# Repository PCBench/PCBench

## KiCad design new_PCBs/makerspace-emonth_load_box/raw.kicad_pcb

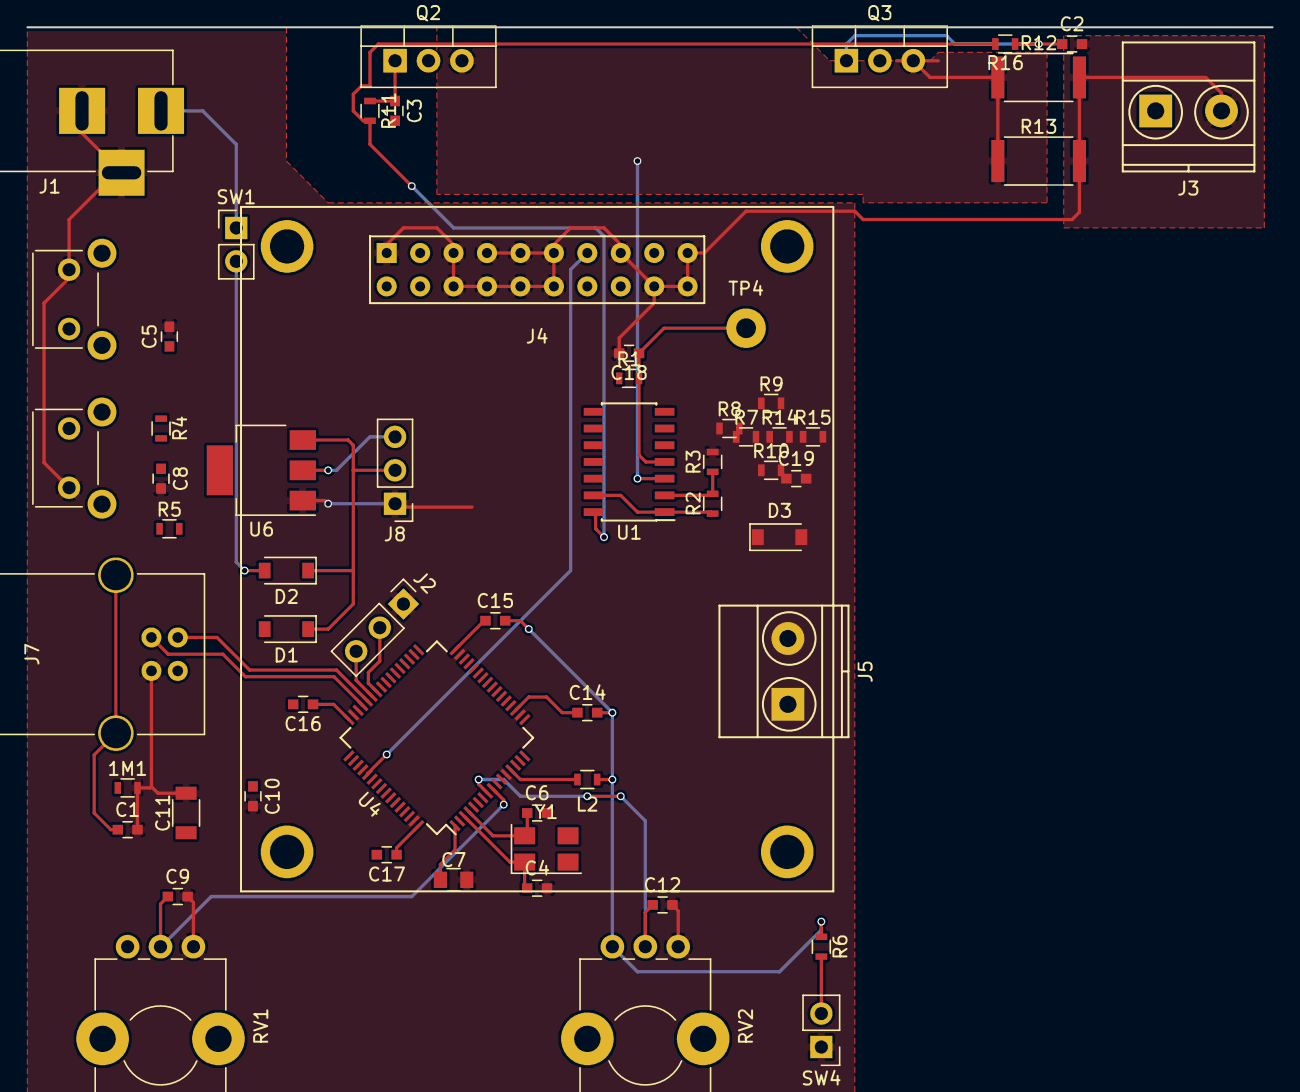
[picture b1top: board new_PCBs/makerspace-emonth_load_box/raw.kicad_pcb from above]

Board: 2 copper layers, 59 parts (0 on the bottom side), 41 nets.

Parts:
1M1: R; R_0603
C1: 4n7; C_0603
C2, C3, C5, C8, C9, C12, C18: 0.1; C_0603
C4, C6, C14, C15, C16, C17: C; C_0603
C7: 1.0; C_0805
C10: 0.1u; C_0603
C11: 10u; C_1206
C19: 4.7n; C_0603
D1, D2: D; D_SOD-123
D3: D_Schottky; D_SOD-123
J1: BARREL_JACK
J2, J8: CONN_01X03; Socket_Strip_Straight_1x03_Pitch2.54mm
J3, J5: Screw_Terminal_1x02; TerminalBlock_Pheonix_MKDS1.5-2pol
J4: CONN_02X10; NHD-1.69
J7: USB_B
L2: Ferrite_Bead; L_0603
Q2, Q3: FQP30N06L; TO-220_Vertical
R1, R4, R11, R16: 100R; R_0603
R2: 24K; R_0603
R3, R6, R9, R14: 10K; R_0603
R5, R10: 4.7K; R_0603
R7, R8, R15: 100K; R_0603
R12, R13: 0R1; R_2512
RV1, RV2: POT; Potentiometer_Alps_RK09K_Horizontal
SW1: SW_SPST; Socket_Strip_Straight_1x02_Pitch2.54mm
SW2, SW3: SW_Push; SW_Tactile_SKHH_Angled
SW4: SW_Push; Pin_Header_Straight_1x02_Pitch2.54mm
TP4: TEST; Measurement_Point_Round-TH_Big
U1: LM324; SOIC-14_3.9x8.7mm_Pitch1.27mm
U4: STM32L152RCTx; LQFP-64_10x10mm_Pitch0.5mm
U6: LD1117S33TR; SOT-223
Y1: Crystal_GND23; Crystal_SMD_5032-4pin_5.0x3.2mm

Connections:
+3V3: C11.1, C14.2, C15.2, C16.2, C17.2, D3.1, J4.2, J8.3, L2.1, R1.1, R5.1, R6.1, RV1.1, RV2.1, U6.2
+12V: D2.2, SW1.2
+BATT: C10.1, D1.1, D2.1, J8.2, U6.3
/load_box_display/MOSI: J4.13, U4.53
/load_box_interface/GO_BUTTON: R6.2, SW4.2
/load_box_interface/STATIC_VREF: C12.1, RV2.2, U4.8
/load_box_interface/STEP_VREF: C9.1, RV1.2, U4.9
/load_box_interface/USER_BUTTON: R4.1, R5.2, SW3.1, U4.2
/load_box_mcu/CHOSEN_VREF: U1.12, U4.40
/load_box_mcu/USB_DM: J7.2, U4.44
/load_box_mcu/USB_DP: J7.3, U4.45
/load_box_sink/REMOTE_SENSE_OUT: C19.1, D3.2, R15.2
GND: 1M1.2, C1.2, C2.2, C3.2, C4.2, C5.2, C6.2, C7.2, C8.2, C9.2, C10.2, C11.2, C12.2, C18.2, C19.2, J1.2, J1.3, J2.1, J3.2, J4.1, J4.5, J4.6, J4.7, J4.8, J4.9, J4.10, J4.11, J4.12, J4.15, J4.18, J4.19, J4.20, J7.4, J8.1, R3.2, R9.2, R10.1, R12.2, R13.2, RV1.3, RV2.3, SW2.1, SW3.2, SW4.1, U4.12, U4.18, U4.31, U4.47, U4.63, U6.1
NRST: C5.1, SW2.2, U4.7
unnamed: 1M1.1, C1.1, J7.5
unnamed: C2.1, Q3.1, R16.1
unnamed: C3.1, Q2.1, R11.1
unnamed: C4.1, U4.3, Y1.1
unnamed: C6.1, U4.4, Y1.4
unnamed: C7.1, U4.1
unnamed: C8.1, R4.2
unnamed: C14.1, U4.19
unnamed: C15.1, U4.32
unnamed: C16.1, U4.48
unnamed: C17.1, U4.64
unnamed: C18.1, R1.2, TP4.1, U1.4
unnamed: D1.2, J7.1
unnamed: J1.1, SW1.1
unnamed: J2.2, U4.42
unnamed: J2.3, U4.43
unnamed: J3.1, Q2.2, Q3.2
unnamed: J5.1, R7.2
unnamed: J5.2, R8.2
unnamed: L2.2, U4.13
unnamed: Q2.3, Q3.3, R12.1, R13.1, U1.3
unnamed: R2.1, U1.1, U1.13
unnamed: R2.2, R3.1, U1.2
unnamed: R7.1, R9.1, U1.10
unnamed: R8.1, R10.2, R14.1, U1.9
unnamed: R11.2, R16.2, U1.14
unnamed: R14.2, R15.1, U1.8

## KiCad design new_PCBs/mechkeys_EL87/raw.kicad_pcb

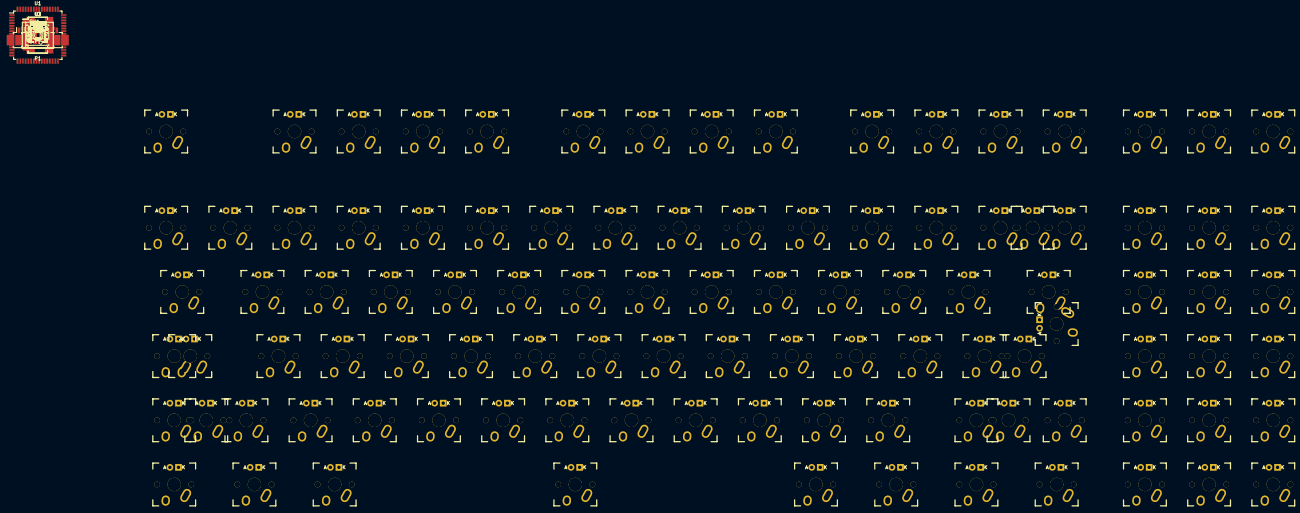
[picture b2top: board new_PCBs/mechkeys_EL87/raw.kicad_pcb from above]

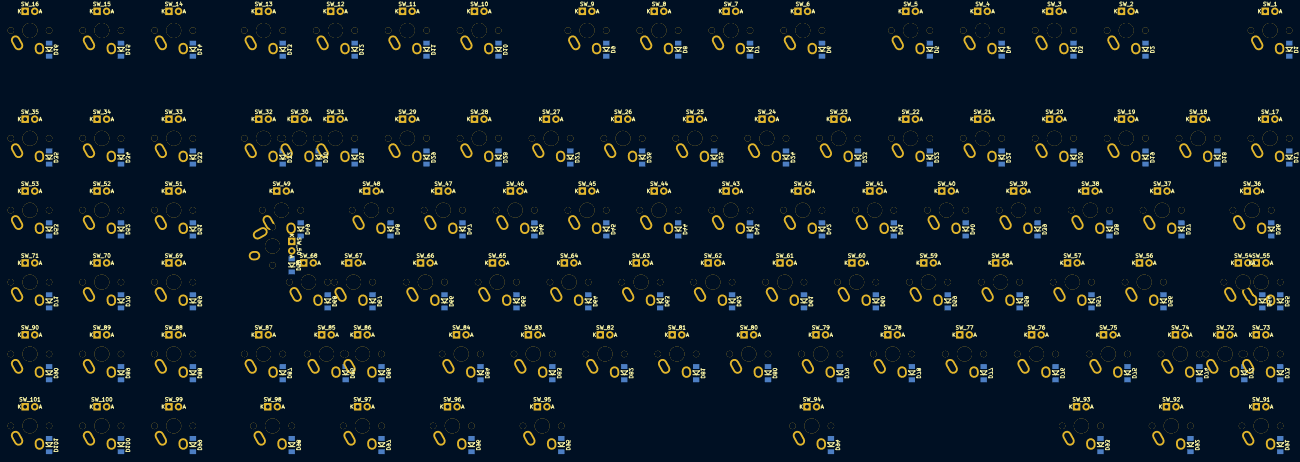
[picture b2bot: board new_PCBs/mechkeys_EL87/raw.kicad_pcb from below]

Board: 2 copper layers, 272 parts (101 on the bottom side), 189 nets, no tracks yet.

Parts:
C1, C2: 18pF; C_0805_HandSoldering
C3, C6, C7, C8, C9, C11, C12, C14, C15: 0.1µF; C_0805_HandSoldering
C4, C10, C13: 1µF; C_0805_HandSoldering
C5: 4.7µF; Tantalum_Case-S_EIA-3216-12_Reflow
D1, D2, D3, D4, D5, D6, D7, D8, D9, D10, D11, D12, D13, D14, D15, D16, D17, D18, D19, D20, D21, D22, D23, D24, D25, D26, D27, D28, D29, D30, D31, D32, D33, D34, D35, D36, D37, D38, D39, D40, D41, D42, D43, D44, D45, D46, D47, D48, D49, D50, D51, D52, D53, D54, D55, D56, D57, D58, D59, D60, D61, D62, D63, D64, D65, D66, D67, D68, D69, D70, D71, D72, D73, D74, D75, D76, D77, D78, D79, D80, D81, D82, D83, D84, D85, D86, D87, D88, D89, D90, D91, D92, D93, D94, D95, D96, D97, D98, D99, D100, D101: D; MiniMELF_Standard
F1: FP_Small; R_1206_HandSoldering
P1: USB_OTG; USB_Mini-B
P2: CONN_02X03; Molex_PicoBlade_53261-0671_06x1.25mm_Angled
P3: CONN_02X05; Molex_PicoBlade_53261-1071_10x1.25mm_Angled
P4: CONN_01X03; Molex_PicoBlade_53261-0371_03x1.25mm_Angled
R1: 10kΩ; R_0805_HandSoldering
R2, R3: 4.7kΩ; R_0805_HandSoldering
R4, R5: 22Ω; R_0805_HandSoldering
R6: 150; R_0805_HandSoldering
R7, R8: 120; R_0805_HandSoldering
R11, R13: 10KΩ; R_0805_HandSoldering
R12, R14: 20KΩ; R_0805_HandSoldering
RGB1, RGB2, RGB3, RGB4, RGB5, RGB6, RGB7, RGB8, RGB9, RGB10, RGB11, RGB12, RGB13, RGB14, RGB15, RGB16, RGB17, RGB18, RGB19, RGB20, RGB21, RGB22, RGB23, RGB24, RGB25, RGB26, RGB27, RGB28, RGB29, RGB30, RGB31, RGB32: Led_RGB_CA; SMP4-RGB
RGB33: Led_RGB_CA; SMP4-RGB-PIPE
SW1: SW_PUSH; SW_SPST_EVQP0
SW_1, SW_2, SW_3, SW_4, SW_5, SW_6, SW_7, SW_8, SW_9, SW_10, SW_11, SW_12, SW_13, SW_14, SW_15, SW_16, SW_17, SW_18, SW_19, SW_20, SW_21, SW_22, SW_23, SW_24, SW_25, SW_26, SW_27, SW_28, SW_29, SW_30, SW_31, SW_32, SW_33, SW_34, SW_35, SW_36, SW_37, SW_38, SW_39, SW_40, SW_41, SW_42, SW_43, SW_44, SW_45, SW_46, SW_47, SW_48, SW_49, SW_50, SW_51, SW_52, SW_53, SW_54, SW_55, SW_56, SW_57, SW_58, SW_59, SW_60, SW_61, SW_62, SW_63, SW_64, SW_65, SW_66, SW_67, SW_68, SW_69, SW_70, SW_71, SW_72, SW_73, SW_74, SW_75, SW_76, SW_77, SW_78, SW_79, SW_80, SW_81, SW_82, SW_83, SW_84, SW_85, SW_86, SW_87, SW_88, SW_89, SW_90, SW_91, SW_92, SW_93, SW_94, SW_95, SW_96, SW_97, SW_98, SW_99, SW_100, SW_101: MX_LED; MXALPS
U1: AT90USB1286; TQFP-64_14x14mm_Pitch0.8mm
U2, U3: IS31FL3731; SSOP-28_5.3x10.2mm_Pitch0.65mm
Y1: 16Mhz; Crystal_SMD_5032_4Pads

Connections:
+5V: C5.1, C6.1, C7.1, C8.1, C9.1, C10.1, C11.1, C13.1, C14.1, F1.2, P2.2, P3.4, P4.2, R1.1, R2.1, R3.1, R11.2, R13.2, RGB33.1, U1.3, U1.8, U1.21, U1.52, U1.64, U2.2, U3.2, U3.18
AUDIO: P4.3, U1.41
C1: SW_1.SW1, SW_17.SW1, SW_36.SW1, SW_54.SW2, SW_55.SW1, SW_72.SW1, SW_73.SW1, SW_91.SW1, U1.51
C2: SW_18.SW1, SW_37.SW1, SW_56.SW1, SW_74.SW1, SW_92.SW1, U1.50
C3: SW_2.SW1, SW_19.SW1, SW_38.SW1, SW_57.SW1, SW_75.SW1, SW_93.SW1, U1.49
C4: SW_3.SW1, SW_20.SW1, SW_39.SW1, SW_58.SW1, SW_76.SW1, U1.48
C5: SW_4.SW1, SW_21.SW1, SW_40.SW1, SW_59.SW1, SW_77.SW1, U1.47
C6: SW_5.SW1, SW_22.SW1, SW_41.SW1, SW_60.SW1, SW_78.SW1, U1.46
C7: SW_6.SW1, SW_23.SW1, SW_42.SW1, SW_61.SW1, SW_79.SW1, SW_94.SW1, U1.45
C8: SW_7.SW1, SW_24.SW1, SW_43.SW1, SW_62.SW1, SW_80.SW1, U1.44
C9: SW_8.SW1, SW_25.SW1, SW_44.SW1, SW_63.SW1, SW_81.SW1, U1.1
C10: SW_9.SW1, SW_26.SW1, SW_45.SW1, SW_64.SW1, SW_82.SW1, U1.2
C11: SW_10.SW1, SW_27.SW1, SW_46.SW1, SW_65.SW1, SW_83.SW1, SW_95.SW1, U1.61
C12: SW_11.SW1, SW_28.SW1, SW_47.SW1, SW_66.SW1, SW_84.SW1, SW_96.SW1, U1.60
C13: SW_12.SW1, SW_29.SW1, SW_48.SW1, SW_67.SW1, SW_68.SW1, SW_85.SW1, SW_86.SW1, SW_97.SW1, U1.59
C14: SW_13.SW1, SW_30.SW1, SW_31.SW1, SW_32.SW1, SW_49.SW1, SW_50.SW1, SW_87.SW1, SW_98.SW1, U1.58
C15: SW_14.SW1, SW_33.SW1, SW_51.SW1, SW_69.SW1, SW_88.SW1, SW_99.SW1, U1.35
C16: SW_15.SW1, SW_34.SW1, SW_52.SW1, SW_70.SW1, SW_89.SW1, SW_100.SW1, U1.36
C17: SW_16.SW1, SW_35.SW1, SW_53.SW1, SW_71.SW1, SW_90.SW1, SW_101.SW1, U1.37
D+: R5.1, U1.5
D-: R4.1, U1.4
GND: C1.2, C2.2, C3.2, C4.2, C5.2, C6.2, C7.2, C8.2, C9.2, C10.2, C11.2, C12.2, C13.2, C14.2, C15.2, P1.5, P1.6, P2.6, P3.2, P3.10, P4.1, R12.2, R14.2, SW1.1, U1.6, U1.22, U1.43, U1.53, U1.63, U2.5, U2.18, U3.5
LED_SCL: R2.2, U1.25, U2.20, U3.20
LED_SDA: R3.2, U1.26, U2.19, U3.19
L_CA1: SW_1.A, SW_2.A, SW_3.A, SW_4.A, SW_5.A, SW_6.A, SW_7.A, SW_8.A, SW_9.K, SW_27.K, SW_46.K, SW_63.K, SW_79.K, SW_80.K, U2.21
L_CA2: SW_8.K, SW_9.A, SW_19.A, SW_20.A, SW_21.A, SW_22.A, SW_23.A, SW_24.A, SW_25.A, SW_26.K, SW_45.K, SW_62.K, U2.22
L_CA3: SW_7.K, SW_25.K, SW_26.A, SW_27.A, SW_38.A, SW_39.A, SW_40.A, SW_41.A, SW_42.A, SW_43.A, SW_44.K, SW_61.K, U2.23
L_CA4: SW_6.K, SW_24.K, SW_43.K, SW_44.A, SW_45.A, SW_46.A, SW_54.A, SW_55.A, SW_56.A, SW_57.A, SW_58.A, SW_59.A, SW_60.K, U2.24
L_CA5: SW_5.K, SW_23.K, SW_42.K, SW_59.K, SW_60.A, SW_61.A, SW_62.A, SW_63.A, SW_71.A, SW_72.A, SW_73.A, SW_74.A, SW_75.A, SW_76.A, SW_77.K, SW_78.K, U2.25
L_CA6: SW_4.K, SW_22.K, SW_41.K, SW_58.K, SW_75.K, SW_76.K, SW_77.A, SW_78.A, SW_79.A, SW_80.A, U2.26
L_CA7: SW_3.K, SW_21.K, SW_40.K, SW_56.K, SW_57.K, SW_73.K, SW_74.K, U2.27
L_CA8: SW_2.K, SW_20.K, SW_39.K, SW_55.K, SW_72.K, U2.28
L_CA9: SW_1.K, SW_19.K, SW_38.K, SW_54.K, SW_71.K, U2.1
L_CB1: SW_10.A, SW_11.A, SW_12.A, SW_13.A, SW_14.A, SW_15.A, SW_16.A, SW_17.A, SW_18.K, SW_37.K, SW_91.K, U2.7
L_CB2: SW_17.K, SW_18.A, SW_28.A, SW_29.A, SW_30.A, SW_31.A, SW_32.A, SW_33.A, SW_34.A, SW_35.A, SW_36.K, SW_70.K, SW_90.K, U2.8
L_CB3: SW_16.K, SW_34.K, SW_35.K, SW_36.A, SW_37.A, SW_47.A, SW_48.A, SW_49.A, SW_50.A, SW_51.A, SW_52.K, SW_53.A, SW_89.K, U2.9
L_CB4: SW_15.K, SW_33.K, SW_52.A, SW_53.K, SW_64.A, SW_65.A, SW_66.A, SW_67.A, SW_68.A, SW_69.K, SW_85.K, SW_86.K, SW_87.K, SW_88.K, U2.10
L_CB5: SW_14.K, SW_32.K, SW_51.K, SW_68.K, SW_69.A, SW_70.A, SW_81.A, SW_82.K, SW_83.K, SW_84.K, U2.11
L_CB6: SW_13.K, SW_31.K, SW_50.K, SW_67.K, SW_81.K, U2.12
L_CB7: SW_12.K, SW_30.K, SW_49.K, SW_66.K, SW_82.A, SW_83.A, SW_84.A, SW_85.A, SW_86.A, SW_87.A, SW_88.A, SW_89.A, SW_90.A, SW_91.A, U2.13
L_CB8: SW_11.K, SW_29.K, SW_48.K, SW_65.K, U2.14
L_CB9: SW_10.K, SW_28.K, SW_47.K, SW_64.K, U2.15
MISO: P2.1, U1.13
MOSI: P2.4, U1.12
unnamed: C1.1, U1.24, Y1.1
unnamed: C2.1, U1.23, Y1.2
unnamed: C3.1, U1.7
unnamed: C4.1, U1.62
unnamed: C12.1, U2.16
unnamed: C15.1, U3.16
unnamed: D1.2, SW_1.SW2
unnamed: D2.2, SW_2.SW2
unnamed: D3.2, SW_3.SW2
unnamed: D4.2, SW_4.SW2
unnamed: D5.2, SW_5.SW2
unnamed: D6.2, SW_6.SW2
unnamed: D7.2, SW_7.SW2
unnamed: D8.2, SW_8.SW2
unnamed: D9.2, SW_9.SW2
unnamed: D10.2, SW_10.SW2
unnamed: D11.2, SW_11.SW2
unnamed: D12.2, SW_12.SW2
unnamed: D13.2, SW_13.SW2
unnamed: D14.2, SW_14.SW2
unnamed: D15.2, SW_15.SW2
unnamed: D16.2, SW_16.SW2
unnamed: D17.2, SW_17.SW2
unnamed: D18.2, SW_18.SW2
unnamed: D19.2, SW_19.SW2
unnamed: D20.2, SW_20.SW2
unnamed: D21.2, SW_21.SW2
unnamed: D22.2, SW_22.SW2
unnamed: D23.2, SW_23.SW2
unnamed: D24.2, SW_24.SW2
unnamed: D25.2, SW_25.SW2
unnamed: D26.2, SW_26.SW2
unnamed: D27.2, SW_27.SW2
unnamed: D28.2, SW_28.SW2
unnamed: D29.2, SW_29.SW2
unnamed: D31.2, SW_30.SW2, SW_31.SW2
unnamed: D32.2, SW_32.SW2
unnamed: D33.1, D34.1, D35.1
unnamed: D33.2, SW_33.SW2
unnamed: D34.2, SW_34.SW2
unnamed: D35.2, SW_35.SW2
unnamed: D36.2, SW_36.SW2
unnamed: D37.2, SW_37.SW2
unnamed: D38.2, SW_38.SW2
unnamed: D39.2, SW_39.SW2
unnamed: D40.2, SW_40.SW2
unnamed: D41.2, SW_41.SW2
unnamed: D42.2, SW_42.SW2
unnamed: D43.2, SW_43.SW2
unnamed: D44.2, SW_44.SW2
unnamed: D45.2, SW_45.SW2
unnamed: D46.2, SW_46.SW2
unnamed: D47.2, SW_47.SW2
unnamed: D48.2, SW_48.SW2
unnamed: D49.2, SW_49.SW2, SW_50.SW2
unnamed: D51.2, SW_51.SW2
unnamed: D52.2, SW_52.SW2
unnamed: D53.2, SW_53.SW2
unnamed: D54.2, SW_54.SW1, SW_55.SW2
unnamed: D56.2, SW_56.SW2
unnamed: D57.2, SW_57.SW2
unnamed: D58.2, SW_58.SW2
unnamed: D59.2, SW_59.SW2
unnamed: D60.2, SW_60.SW2
unnamed: D61.2, SW_61.SW2
unnamed: D62.2, SW_62.SW2
unnamed: D63.2, SW_63.SW2
unnamed: D64.2, SW_64.SW2
unnamed: D65.2, SW_65.SW2
unnamed: D66.2, SW_66.SW2
unnamed: D67.2, SW_67.SW2, SW_68.SW2
unnamed: D69.2, SW_69.SW2
unnamed: D70.2, SW_70.SW2
unnamed: D71.2, SW_71.SW2
unnamed: D72.2, SW_72.SW2, SW_73.SW2
unnamed: D74.2, SW_74.SW2
unnamed: D75.2, SW_75.SW2
unnamed: D76.2, SW_76.SW2
unnamed: D77.2, SW_77.SW2
unnamed: D78.2, SW_78.SW2
unnamed: D79.2, SW_79.SW2
unnamed: D80.2, SW_80.SW2
unnamed: D81.2, SW_81.SW2
unnamed: D82.2, SW_82.SW2
unnamed: D83.2, SW_83.SW2
unnamed: D84.2, SW_84.SW2
unnamed: D85.2, SW_85.SW2, SW_86.SW2
unnamed: D87.2, SW_87.SW2
unnamed: D88.2, SW_88.SW2
unnamed: D89.2, SW_89.SW2
unnamed: D90.2, SW_90.SW2
unnamed: D91.2, SW_91.SW2
unnamed: D92.2, SW_92.SW2
unnamed: D93.2, SW_93.SW2
unnamed: D94.2, SW_94.SW2
unnamed: D95.2, SW_95.SW2
unnamed: D96.2, SW_96.SW2
unnamed: D97.2, SW_97.SW2
unnamed: D98.2, SW_98.SW2
unnamed: D99.2, SW_99.SW2
unnamed: D100.2, SW_100.SW2
unnamed: D101.2, SW_101.SW2
unnamed: F1.1, P1.1
unnamed: R6.1, RGB33.2
unnamed: R7.1, RGB33.3
unnamed: R8.1, RGB33.4
unnamed: R11.1, U2.3
unnamed: R12.1, U2.6
unnamed: R13.1, U3.3
unnamed: R14.1, U3.6
PWM_BLUE: R8.2, U1.17
PWM_GREEN: R7.2, U1.16
PWM_RED: R6.2, U1.15
R1: D1.1, D2.1, D3.1, D4.1, D5.1, D6.1, D7.1, D8.1, D9.1, D10.1, D11.1, D12.1, D13.1, D14.1, D15.1, D16.1, U1.27
R2: D17.1, D18.1, D19.1, D20.1, D23.1, D24.1, D25.1, D26.1, D27.1, D28.1, D29.1, D31.1, U1.28
R3: D36.1, D37.1, D38.1, D39.1, D41.1, D42.1, D43.1, D44.1, D45.1, D46.1, D47.1, D48.1, D49.1, D51.1, D52.1, D53.1, U1.29
R4: D32.1, D54.1, D56.1, D57.1, D58.1, D59.1, D60.1, D61.1, D62.1, D63.1, D64.1, D65.1, D66.1, D67.1, D69.1, D70.1, D71.1, U1.30
R5: D72.1, D74.1, D75.1, D76.1, D77.1, D78.1, D79.1, D80.1, D81.1, D82.1, D83.1, D84.1, D85.1, D87.1, D88.1, D89.1, D90.1, U1.31
R6: D91.1, D92.1, D93.1, D94.1, D95.1, D96.1, D97.1, D99.1, D100.1, D101.1, U1.32
RESET: P2.5, P3.6, R1.2, SW1.2, U1.20
R_CA1: RGB1.2, RGB2.2, RGB3.2, RGB4.2, RGB5.2, RGB6.2, RGB7.2, RGB8.2, RGB9.1, U3.21
R_CA2: RGB1.1, RGB2.3, RGB3.3, RGB4.3, RGB5.3, RGB6.3, RGB7.3, RGB8.3, RGB10.1, U3.22
R_CA3: RGB1.3, RGB2.1, RGB3.4, RGB4.4, RGB5.4, RGB6.4, RGB7.4, RGB8.4, RGB11.1, U3.23
R_CA4: RGB1.4, RGB2.4, RGB3.1, RGB12.1, U3.24
R_CA5: RGB4.1, RGB13.1, U3.25
R_CA6: RGB5.1, RGB14.1, RGB15.4, RGB16.4, U3.26
R_CA7: RGB6.1, RGB9.4, RGB10.4, RGB11.4, RGB12.4, RGB13.4, RGB14.4, RGB15.1, RGB16.3, U3.27
R_CA8: RGB7.1, RGB9.3, RGB10.3, RGB11.3, RGB12.3, RGB13.3, RGB14.3, RGB15.3, RGB16.1, U3.28
R_CA9: RGB8.1, RGB9.2, RGB10.2, RGB11.2, RGB12.2, RGB13.2, RGB14.2, RGB15.2, RGB16.2, U3.1
R_CB1: RGB17.2, RGB18.2, RGB19.2, RGB20.2, RGB21.2, RGB22.2, RGB23.2, RGB24.2, RGB25.1, U3.7
R_CB2: RGB17.1, RGB18.3, RGB19.3, RGB20.3, RGB21.3, RGB22.3, RGB23.3, RGB24.3, RGB26.1, U3.8
R_CB3: RGB17.3, RGB18.1, RGB19.4, RGB20.4, RGB21.4, RGB22.4, RGB23.4, RGB24.4, RGB27.1, U3.9
R_CB4: RGB17.4, RGB18.4, RGB19.1, RGB28.1, U3.10
R_CB5: RGB20.1, RGB29.1, U3.11
R_CB6: RGB21.1, RGB30.1, RGB31.4, RGB32.4, U3.12
R_CB7: RGB22.1, RGB25.4, RGB26.4, RGB27.4, RGB28.4, RGB29.4, RGB30.4, RGB31.1, RGB32.3, U3.13
R_CB8: RGB23.1, RGB25.3, RGB26.3, RGB27.3, RGB28.3, RGB29.3, RGB30.3, RGB31.3, RGB32.1, U3.14
R_CB9: RGB24.1, RGB25.2, RGB26.2, RGB27.2, RGB28.2, RGB29.2, RGB30.2, RGB31.2, RGB32.2, U3.15
SCK: P2.3, U1.11
TCK: P3.1, U1.57
TDI: P3.9, U1.54
TDO: P3.3, U1.55
TMS: P3.5, U1.56
USB+: P1.4, R5.2
USB-: P1.3, R4.2

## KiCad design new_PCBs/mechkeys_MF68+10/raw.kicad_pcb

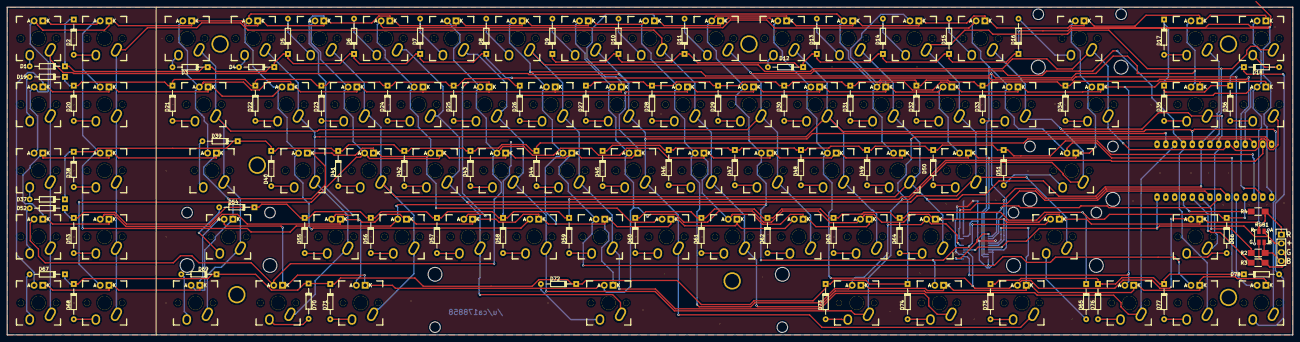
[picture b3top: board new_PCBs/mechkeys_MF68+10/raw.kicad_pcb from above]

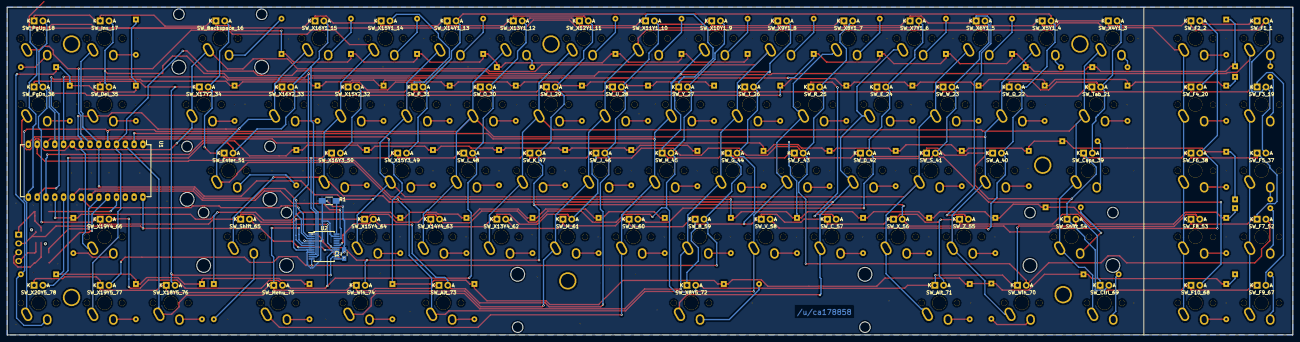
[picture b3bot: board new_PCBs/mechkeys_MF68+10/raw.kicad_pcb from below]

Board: 2 copper layers, 370.5 x 94.4 mm, 170 parts (4 on the bottom side), 119 nets.

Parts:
C1: 1µF; C_0805_HandSoldering
CHERRY: MX; CHERRY_PCB_275H_STABILIZER
CHERRY#2, CHERRY#4: MX; CHERRY_PCB_225H_STABILIZER
CHERRY#3: MX; CHERRY_PCB_625H_STABILIZER
CHERRY#5: MX; CHERRY_PCB_200H_STABILIZER
D1, D2, D3, D4, D5, D6, D7, D8, D9, D10, D11, D12, D13, D14, D15, D16, D17, D18, D19, D20, D21, D22, D23, D24, D25, D26, D27, D28, D29, D30, D31, D32, D33, D34, D35, D36, D37, D38, D39, D40, D41, D42, D43, D44, D45, D46, D47, D48, D49, D50, D51, D52, D53, D54, D55, D56, D57, D58, D59, D60, D61, D62, D63, D64, D65, D66, D67, D68, D69, D70, D71, D72, D73, D74, D75, D76, D77, D78: D; Diode_DO-35_SOD27_Horizontal_RM10
GND: MountingHole_5.3mm_M5
R1: 39kΩ; R_1206_HandSoldering
R2: 150Ω; R_1206_HandSoldering
R3, R4: 120Ω; R_1206_HandSoldering
RGB1: Led_RGB_CA; SMP4-RGB
SW_A_40: MX_LED; MXALPS
SW_Alt_71, SW_Alt_73: MX_LED; MXALPS
SW_B_59: MX_LED; MXALPS
SW_Backspace_16: MX_LED; MXALPS
SW_C_57: MX_LED; MXALPS
SW_Caps_39: MX_LED; MXALPS
SW_Ctrl_69: MX_LED; MXALPS
SW_D_42: MX_LED; MXALPS
SW_Del_35: MX_LED; MXALPS
SW_E_24: MX_LED; MXALPS
SW_Enter_51: MX_LED; MXALPS
SW_F1_1, SW_F2_2, SW_F3_19, SW_F4_20, SW_F5_37, SW_F6_38, SW_F7_52, SW_F8_53, SW_F9_67, SW_F10_68: MX_LED; MXALPS
SW_F_43: MX_LED; MXALPS
SW_G_44: MX_LED; MXALPS
SW_H_45: MX_LED; MXALPS
SW_I_29: MX_LED; MXALPS
SW_Ins_17: MX_LED; MXALPS
SW_J_46: MX_LED; MXALPS
SW_K_47: MX_LED; MXALPS
SW_L_48: MX_LED; MXALPS
SW_M_61: MX_LED; MXALPS
SW_Menu_75: MX_LED; MXALPS
SW_N_60: MX_LED; MXALPS
SW_O_30: MX_LED; MXALPS
SW_P_31: MX_LED; MXALPS
SW_PgDn_36: MX_LED; MXALPS
SW_PgUp_18: MX_LED; MXALPS
SW_Q_22: MX_LED; MXALPS
SW_R_25: MX_LED; MXALPS
SW_S_41: MX_LED; MXALPS
SW_Shift_54, SW_Shift_65: MX_LED; MXALPS
SW_T_26: MX_LED; MXALPS
SW_Tab_21: MX_LED; MXALPS
SW_U_28: MX_LED; MXALPS
SW_V_58: MX_LED; MXALPS
SW_W_23: MX_LED; MXALPS
SW_Win_70, SW_Win_74: MX_LED; MXALPS
SW_X4Y1_3, SW_X5Y1_4, SW_X6Y1_5, SW_X7Y1_6, SW_X8Y1_7, SW_X8Y5_72, SW_X9Y1_8, SW_X10Y1_9, SW_X11Y1_10, SW_X12Y1_11, SW_X13Y1_12, SW_X13Y4_62, SW_X14Y1_13, SW_X14Y4_63, SW_X15Y1_14, SW_X15Y2_32, SW_X15Y3_49, SW_X15Y4_64, SW_X16Y1_15, SW_X16Y2_33, SW_X16Y3_50, SW_X17Y2_34, SW_X18Y5_76, SW_X19Y4_66, SW_X19Y5_77, SW_X20Y5_78: MX_LED; MXALPS
SW_X_56: MX_LED; MXALPS
SW_Y_27: MX_LED; MXALPS
SW_Z_55: MX_LED; MXALPS
U1: Teensy_3.2; Teensy3.2
U2: AN32183A; SSOP-24_5.3x8.2mm_Pitch0.65mm

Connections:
+5V: RGB1.1, U1.Vin, U2.7, U2.17
C1: SW_F1_1.SW1, SW_F3_19.SW1, SW_F5_37.SW1, SW_F7_52.SW1, SW_F9_67.SW1, SW_H_45.SW1, SW_Menu_75.SW1, SW_N_60.SW1, SW_X10Y1_9.SW1, SW_Y_27.SW1, U1.0
C2: SW_F2_2.SW1, SW_F4_20.SW1, SW_F6_38.SW1, SW_F8_53.SW1, SW_F10_68.SW1, SW_J_46.SW1, SW_M_61.SW1, SW_U_28.SW1, SW_X11Y1_10.SW1, SW_X18Y5_76.SW1, U1.1
C3: SW_Caps_39.SW1, SW_Ctrl_69.SW1, SW_I_29.SW1, SW_K_47.SW1, SW_Shift_54.SW1, SW_Tab_21.SW1, SW_X4Y1_3.SW1, SW_X12Y1_11.SW1, SW_X13Y4_62.SW1, SW_X19Y5_77.SW1, U1.2
C4: SW_A_40.SW1, SW_L_48.SW1, SW_O_30.SW1, SW_Q_22.SW1, SW_Win_70.SW1, SW_X5Y1_4.SW1, SW_X13Y1_12.SW1, SW_X14Y4_63.SW1, SW_X20Y5_78.SW1, SW_Z_55.SW1, U1.3
C5: SW_Alt_71.SW1, SW_Ins_17.SW1, SW_P_31.SW1, SW_S_41.SW1, SW_W_23.SW1, SW_X6Y1_5.SW1, SW_X14Y1_13.SW1, SW_X15Y3_49.SW1, SW_X15Y4_64.SW1, SW_X_56.SW1, U1.4
C6: SW_C_57.SW1, SW_D_42.SW1, SW_E_24.SW1, SW_PgUp_18.SW1, SW_Shift_65.SW1, SW_X7Y1_6.SW1, SW_X8Y5_72.SW1, SW_X15Y1_14.SW1, SW_X15Y2_32.SW1, SW_X16Y3_50.SW1, U1.5
C7: SW_Alt_73.SW1, SW_Del_35.SW1, SW_Enter_51.SW1, SW_F_43.SW1, SW_R_25.SW1, SW_V_58.SW1, SW_X8Y1_7.SW1, SW_X16Y1_15.SW1, SW_X16Y2_33.SW1, SW_X19Y4_66.SW1, U1.6
C8: SW_B_59.SW1, SW_Backspace_16.SW1, SW_G_44.SW1, SW_PgDn_36.SW1, SW_T_26.SW1, SW_Win_74.SW1, SW_X9Y1_8.SW1, SW_X17Y2_34.SW1, U1.7
GND: C1.2, R1.2, U1.GND0, U2.4, U2.9, U2.15, U2.23
NSRT: U1.20, U2.22
unnamed: C1.1, U2.1, U2.13
unnamed: D1.2, SW_F1_1.SW2
unnamed: D2.2, SW_F2_2.SW2
unnamed: D3.2, SW_X4Y1_3.SW2
unnamed: D4.2, SW_X5Y1_4.SW2
unnamed: D5.2, SW_X6Y1_5.SW2
unnamed: D6.2, SW_X7Y1_6.SW2
unnamed: D7.2, SW_X8Y1_7.SW2
unnamed: D8.2, SW_X9Y1_8.SW2
unnamed: D9.2, SW_X10Y1_9.SW2
unnamed: D10.2, SW_X11Y1_10.SW2
unnamed: D11.2, SW_X12Y1_11.SW2
unnamed: D12.2, SW_X13Y1_12.SW2
unnamed: D13.2, SW_X14Y1_13.SW2
unnamed: D14.2, SW_X15Y1_14.SW2
unnamed: D15.2, SW_X16Y1_15.SW2
unnamed: D16.2, SW_Backspace_16.SW2
unnamed: D17.1, D18.1, D35.1, D36.1, D78.2, SW_X20Y5_78.SW2
unnamed: D17.2, SW_Ins_17.SW2
unnamed: D18.2, SW_PgUp_18.SW2
unnamed: D19.2, SW_F3_19.SW2
unnamed: D20.2, SW_F4_20.SW2
unnamed: D21.2, SW_Tab_21.SW2
unnamed: D22.2, SW_Q_22.SW2
unnamed: D23.2, SW_W_23.SW2
unnamed: D24.2, SW_E_24.SW2
unnamed: D25.2, SW_R_25.SW2
unnamed: D26.2, SW_T_26.SW2
unnamed: D27.2, SW_Y_27.SW2
unnamed: D28.2, SW_U_28.SW2
unnamed: D29.2, SW_I_29.SW2
unnamed: D30.2, SW_O_30.SW2
unnamed: D31.2, SW_P_31.SW2
unnamed: D32.2, SW_X15Y2_32.SW2
unnamed: D33.2, SW_X16Y2_33.SW2
unnamed: D34.2, SW_X17Y2_34.SW2
unnamed: D35.2, SW_Del_35.SW2
unnamed: D36.2, SW_PgDn_36.SW2
unnamed: D37.2, SW_F5_37.SW2
unnamed: D38.2, SW_F6_38.SW2
unnamed: D39.2, SW_Caps_39.SW2
unnamed: D40.2, SW_A_40.SW2
unnamed: D41.2, SW_S_41.SW2
unnamed: D42.2, SW_D_42.SW2
unnamed: D43.2, SW_F_43.SW2
unnamed: D44.2, SW_G_44.SW2
unnamed: D45.2, SW_H_45.SW2
unnamed: D46.2, SW_J_46.SW2
unnamed: D47.2, SW_K_47.SW2
unnamed: D48.2, SW_L_48.SW2
unnamed: D49.2, SW_X15Y3_49.SW2
unnamed: D50.2, SW_X16Y3_50.SW2
unnamed: D51.2, SW_Enter_51.SW2
unnamed: D52.2, SW_F7_52.SW2
unnamed: D53.2, SW_F8_53.SW2
unnamed: D54.2, SW_Shift_54.SW2
unnamed: D55.2, SW_Z_55.SW2
unnamed: D56.2, SW_X_56.SW2
unnamed: D57.2, SW_C_57.SW2
unnamed: D58.2, SW_V_58.SW2
unnamed: D59.2, SW_B_59.SW2
unnamed: D60.2, SW_N_60.SW2
unnamed: D61.2, SW_M_61.SW2
unnamed: D62.2, SW_X13Y4_62.SW2
unnamed: D63.2, SW_X14Y4_63.SW2
unnamed: D64.2, SW_X15Y4_64.SW2
unnamed: D65.2, SW_Shift_65.SW2
unnamed: D66.2, SW_X19Y4_66.SW2
unnamed: D67.2, SW_F9_67.SW2
unnamed: D68.2, SW_F10_68.SW2
unnamed: D69.2, SW_Ctrl_69.SW2
unnamed: D70.2, SW_Win_70.SW2
unnamed: D71.2, SW_Alt_71.SW2
unnamed: D72.2, SW_X8Y5_72.SW2
unnamed: D73.2, SW_Alt_73.SW2
unnamed: D74.2, SW_Win_74.SW2
unnamed: D75.2, SW_Menu_75.SW2
unnamed: D76.2, SW_X18Y5_76.SW2
unnamed: D77.2, SW_X19Y5_77.SW2
unnamed: R1.1, U2.24
unnamed: R2.1, RGB1.4
unnamed: R2.2, U1.21
unnamed: R3.1, RGB1.3
unnamed: R3.2, U1.22
unnamed: R4.1, RGB1.2
unnamed: R4.2, U1.23
R1: D1.1, D2.1, D3.1, D4.1, D5.1, D6.1, D7.1, D8.1, U1.8
R2: D19.1, D20.1, D21.1, D22.1, D23.1, D24.1, D25.1, D26.1, U1.9
R3: D37.1, D38.1, D39.1, D40.1, D41.1, D42.1, D43.1, D44.1, U1.10
R4: D52.1, D53.1, D54.1, D55.1, D56.1, D57.1, D58.1, D59.1, U1.11
R5: D67.1, D68.1, D69.1, D70.1, D71.1, D72.1, D73.1, D74.1, U1.12
R6: D9.1, D10.1, D11.1, D12.1, D13.1, D14.1, D15.1, D16.1, U1.13
R7: D27.1, D28.1, D29.1, D30.1, D31.1, D32.1, D33.1, D34.1, U1.14
R8: D45.1, D46.1, D47.1, D48.1, D49.1, D50.1, D51.1, U1.15
R9: D60.1, D61.1, D62.1, D63.1, D64.1, D65.1, D66.1, U1.16
R10: D75.1, D76.1, D77.1, D78.1, U1.17
SCL: U1.19, U2.2
SDA: U1.18, U2.3
Z1: SW_Alt_73.A, SW_F1_1.A, SW_F2_2.K, SW_F3_19.A, SW_F5_37.A, SW_J_46.A, SW_U_28.A, SW_X4Y1_3.K, SW_X5Y1_4.K, SW_X6Y1_5.K, SW_X7Y1_6.K, SW_X8Y1_7.K, SW_X9Y1_8.K, SW_X10Y1_9.K, SW_X11Y1_10.A, SW_X15Y4_64.A, SW_Z_55.A, U2.19
Z2: SW_Backspace_16.K, SW_F1_1.K, SW_F2_2.A, SW_F4_20.A, SW_F6_38.A, SW_I_29.A, SW_Ins_17.K, SW_K_47.A, SW_PgUp_18.K, SW_Shift_65.A, SW_Win_74.A, SW_X12Y1_11.A, SW_X13Y1_12.K, SW_X14Y1_13.K, SW_X15Y1_14.K, SW_X16Y1_15.K, SW_X_56.A, U2.18
Z3: SW_C_57.A, SW_Caps_39.A, SW_E_24.K, SW_L_48.A, SW_Menu_75.A, SW_O_30.A, SW_Q_22.K, SW_R_25.K, SW_T_26.K, SW_Tab_21.A, SW_W_23.K, SW_X4Y1_3.A, SW_X11Y1_10.K, SW_X12Y1_11.K, SW_X13Y1_12.A, SW_X19Y4_66.A, SW_Y_27.K, U2.16
Z4: SW_A_40.A, SW_Del_35.K, SW_F3_19.K, SW_F4_20.K, SW_F9_67.A, SW_P_31.A, SW_PgDn_36.K, SW_Q_22.A, SW_Tab_21.K, SW_V_58.A, SW_X5Y1_4.A, SW_X14Y1_13.A, SW_X15Y2_32.K, SW_X15Y3_49.A, SW_X16Y2_33.K, SW_X17Y2_34.K, SW_X18Y5_76.A, U2.14
Z5: SW_B_59.A, SW_D_42.K, SW_F10_68.A, SW_F_43.K, SW_G_44.K, SW_H_45.K, SW_I_29.K, SW_O_30.K, SW_P_31.K, SW_S_41.A, SW_U_28.K, SW_W_23.A, SW_X6Y1_5.A, SW_X15Y1_14.A, SW_X15Y2_32.A, SW_X16Y3_50.A, SW_X19Y5_77.A, U2.12
Z6: SW_A_40.K, SW_Caps_39.K, SW_Ctrl_69.A, SW_D_42.A, SW_E_24.A, SW_Enter_51.A, SW_F5_37.K, SW_F6_38.K, SW_F7_52.K, SW_F8_53.K, SW_N_60.A, SW_S_41.K, SW_Shift_54.K, SW_X7Y1_6.A, SW_X16Y1_15.A, SW_X16Y2_33.A, SW_X20Y5_78.A, U2.11
Z7: SW_Backspace_16.A, SW_Enter_51.K, SW_F7_52.A, SW_F_43.A, SW_J_46.K, SW_K_47.K, SW_L_48.K, SW_M_61.A, SW_R_25.A, SW_Win_70.A, SW_X8Y1_7.A, SW_X13Y4_62.K, SW_X14Y4_63.K, SW_X15Y3_49.K, SW_X16Y3_50.K, SW_X17Y2_34.A, U2.10
Z8: SW_Alt_71.A, SW_B_59.K, SW_C_57.K, SW_Del_35.A, SW_F8_53.A, SW_G_44.A, SW_Ins_17.A, SW_M_61.K, SW_N_60.K, SW_T_26.A, SW_V_58.K, SW_X8Y5_72.K, SW_X9Y1_8.A, SW_X13Y4_62.A, SW_X_56.K, SW_Z_55.K, U2.8
Z9: SW_Alt_71.K, SW_Ctrl_69.K, SW_F9_67.K, SW_F10_68.K, SW_H_45.A, SW_PgDn_36.A, SW_PgUp_18.A, SW_Shift_54.A, SW_Shift_65.K, SW_Win_70.K, SW_X8Y5_72.A, SW_X10Y1_9.A, SW_X14Y4_63.A, SW_X15Y4_64.K, SW_X19Y4_66.K, SW_Y_27.A, U2.6
Z10: SW_Alt_73.K, SW_Menu_75.K, SW_Win_74.K, SW_X18Y5_76.K, SW_X19Y5_77.K, SW_X20Y5_78.K, U2.5

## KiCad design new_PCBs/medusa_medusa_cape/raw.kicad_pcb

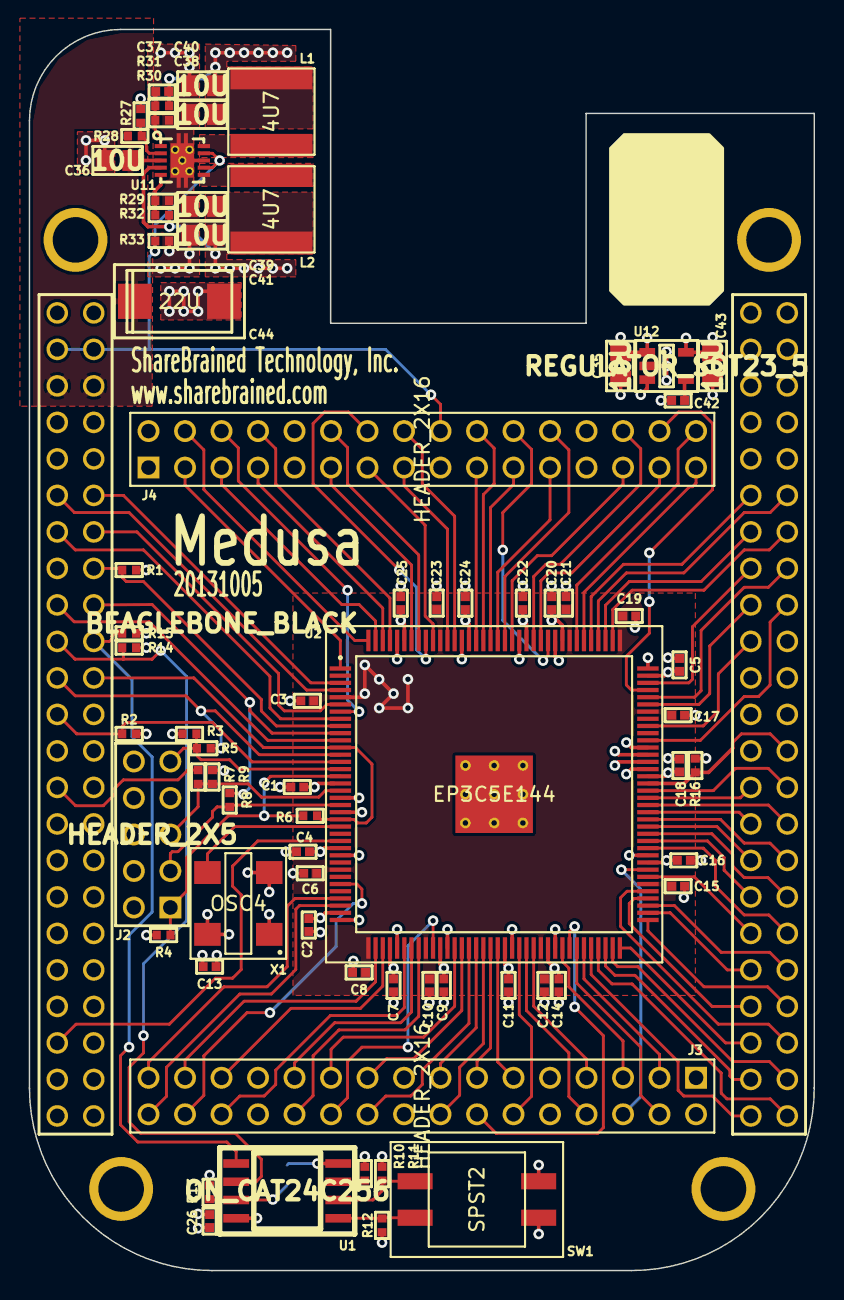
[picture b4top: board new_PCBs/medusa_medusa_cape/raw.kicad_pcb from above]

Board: 4 copper layers, 54.6 x 86.4 mm, 73 parts (0 on the bottom side), 113 nets.

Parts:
C1, C2, C3, C4, C5, C6, C7, C8, C9, C10, C11, C12, C13, C14, C15, C16, C17, C18, C19, C20, C21, C22, C23, C24, C25, C26: 100N; IPC_CAPC1005X55N
C35, C36, C38, C39, C40, C41, C43: 10U; IPC_CAPC2012X140N
C37: 33P; IPC_CAPC1005X55N
C42: DNI; IPC_CAPC1005X55N
C44: 22U; IPC_CAPMP7343X310N
J1: BEAGLEBONE_BLACK; beaglebone_black
J2: HEADER_2X5; HEADER_5X2_TH_254
J3, J4: HEADER_2X16; HEADER_16X2_TH_254
L1, L2: 4U7; NR6028
R1, R2, R3, R9, R10, R11, R12, R13, R14, R15, R16, R28, R33: 10K; IPC_RESC1005X40N
R4: 1K; IPC_RESC1005X40N
R5, R6, R7, R8, R27: DNI; IPC_RESC1005X40N
R29, R30, R31, R32: R; IPC_RESC1005X40N
SW1: SPST2; 219-2MST
TP1, TP2: TP; TP_1MM
U1: ON_CAT24C256; IPC_SOIC127P780X205-8N
U2: EP3C5E144; QFP50P2200X2200X160-145N_ALTERA
U11: TPS62420; TI_DRC_S-PVSON-N10
U12: REGULATOR_SOT23_5; IPC_SOT95P280X110-5N
X1: OSC4; OSCSC508P500X700X180-4N

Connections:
+1.2V: C3.1, C6.1, C8.1, C10.1, C12.1, C15.1, C17.1, C19.1, C21.1, C23.1, C39.2, C41.2, L2.2, R32.2, U2.5, U2.29, U2.37, U2.45, U2.61, U2.78, U2.102, U2.109, U2.116, U2.134, U11.4
+2.5V: C2.1, C5.1, C43.1, U2.35, U2.107, U12.5
+3.3V: C1.1, C4.1, C7.1, C9.1, C11.1, C13.1, C14.1, C16.1, C18.1, C20.1, C22.1, C24.1, C25.1, C26.1, C35.1, C37.2, C38.1, C40.1, J2.4, L1.1, R1.1, R3.1, R9.1, R10.1, R11.1, R12.1, R13.1, R14.1, R15.1, R16.1, R31.2, U1.8, U2.17, U2.26, U2.40, U2.47, U2.56, U2.62, U2.81, U2.93, U2.117, U2.122, U2.130, U2.139, U12.1, U12.3, X1.1, X1.4
/FPGA/AF0: J3.3, U2.67
/FPGA/AF1: J3.4, U2.66
/FPGA/AF2: J3.5, U2.64
/FPGA/AF3: J3.7, U2.60
/FPGA/AF4: J3.8, U2.59
/FPGA/AF5: J3.11, U2.55
/FPGA/AF6: J3.12, U2.58
/FPGA/AF7: J3.13, U2.54
/FPGA/AF8: J3.15, U2.52
/FPGA/AF9: J3.16, U2.53
/FPGA/AF10: J3.19, U2.50
/FPGA/AF11: J3.20, U2.51
/FPGA/AF12: J3.21, U2.49
/FPGA/AF13: J3.23, U2.43
/FPGA/AF14: J3.24, U2.44
/FPGA/AF15: J3.27, U2.39
/FPGA/AF16: J3.28, U2.42
/FPGA/AF17: J3.29, U2.38
/FPGA/AF18: J3.31, U2.33
/FPGA/AF19: J3.32, U2.34
/FPGA/AS0: J3.6, U2.80
/FPGA/AS1: J3.14, U2.65
/FPGA/AS2: J3.22, U2.46
/FPGA/AS3: J3.30, U2.31
/FPGA/BF0: J4.3, U2.1
/FPGA/BF1: J4.4, U2.144
/FPGA/BF2: J4.5, U2.143
/FPGA/BF3: J4.7, U2.142
/FPGA/BF4: J4.8, U2.141
/FPGA/BF5: J4.11, U2.138
/FPGA/BF6: J4.12, U2.137
/FPGA/BF7: J4.13, U2.135
/FPGA/BF8: J4.15, U2.133
/FPGA/BF9: J4.16, U2.132
/FPGA/BF10: J4.19, U2.129
/FPGA/BF11: J4.20, U2.128
/FPGA/BF12: J4.21, U2.127
/FPGA/BF13: J4.23, U2.126
/FPGA/BF14: J4.24, U2.125
/FPGA/BF15: J4.27, U2.124
/FPGA/BF16: J4.28, U2.121
/FPGA/BF17: J4.29, U2.120
/FPGA/BF18: J4.31, U2.114
/FPGA/BF19: J4.32, U2.115
/FPGA/BS0: J4.6, U2.7
/FPGA/BS1: J4.14, U2.136
/FPGA/BS2: J4.22, U2.119
/FPGA/BS3: J4.30, U2.105
/FPGA/CLKOUT2: J1.B41, U2.25
/FPGA/EHRPWM1A: J1.B14, U2.6
/FPGA/EHRPWM1B: J1.B16, R1.2, U2.9
/FPGA/GPIO1_17: J1.B23, R2.1, U2.14
/FPGA/GPIO1_28: J1.B12, U2.3
/FPGA/GPIO1_29: J1.A26, R16.2, U2.92
/FPGA/GPIO2_1: J1.A18, U2.98
/FPGA/GPIO3_19: J1.B27, R7.2
/FPGA/I2C2_SCL: J1.B19, R14.2, U1.6
/FPGA/I2C2_SDA: J1.B20, R15.2, U1.5
/FPGA/LCD_DATA0: J1.A45, U2.68
/FPGA/LCD_DATA1: J1.A46, U2.69
/FPGA/LCD_DATA2: J1.A43, U2.70
/FPGA/LCD_DATA3: J1.A44, U2.71
/FPGA/LCD_DATA4: J1.A41, U2.72
/FPGA/LCD_DATA5: J1.A42, U2.77
/FPGA/LCD_DATA6: J1.A39, U2.76
/FPGA/LCD_DATA7: J1.A40, U2.73
/FPGA/LCD_DATA8: J1.A37, U2.74
/FPGA/LCD_DATA9: J1.A38, U2.75
/FPGA/LCD_DATA10: J1.A36, U2.83
/FPGA/LCD_DATA11: J1.A34, U2.85
/FPGA/LCD_DATA12: J1.A35, U2.79
/FPGA/LCD_DATA13: J1.A33, U2.84
/FPGA/LCD_DATA14: J1.A31, U2.86
/FPGA/LCD_DATA15: J1.A32, U2.87
/FPGA/LCD_DATA16: J1.A15, U2.106
/FPGA/LCD_DATA17: J1.A16, U2.104
/FPGA/LCD_DATA18: J1.A11, U2.113
/FPGA/LCD_DATA19: J1.A12, U2.112
/FPGA/LCD_DATA20: J1.A17, U2.103
/FPGA/LCD_DATA21: J1.A14, U2.110
/FPGA/LCD_DATA22: J1.A13, U2.111
/FPGA/LCD_DATA23: J1.A19, U2.100
/FPGA/LCD_DE: J1.A30, U2.89
/FPGA/LCD_HSYNC: J1.A29, U2.88
/FPGA/LCD_PCLK: J1.A28, U2.91
/FPGA/LCD_VSYNC: J1.A27, U2.90
/FPGA/PWREN: J1.B3, J1.B4, J4.18, R33.2, U11.7, U11.9
/FPGA/REF_CLK: U2.23, X1.3
/FPGA/SPI0_CS0: J1.B17, U2.11
/FPGA/SPI0_D0: J1.B21, R5.2, U2.13
/FPGA/SPI0_D1: J1.B18, R8.2, U2.10
/FPGA/SPI0_SCLK: J1.B22, R6.2, U2.12, U2.22
/FPGA/TCK: J2.1, R4.1, R6.1, U2.16
/FPGA/TDI: J2.9, R3.2, R5.1, U2.15
/FPGA/TDO: J2.3, R8.1, U2.20
/FPGA/TMS: J2.5, R7.1, R9.2, U2.18
/FPGA/UART4_RXD: J1.B11, U2.4
/FPGA/UART4_TXD: J1.B13, U2.8
/FPGA/V_RAW: C36.1, C44.1, J1.B5, J1.B6, J3.2, J3.9, J3.18, J3.25, J4.2, J4.9, J4.25, R28.1, U11.3
GND: C1.2, C2.2, C3.2, C4.2, C5.2, C6.2, C7.2, C8.2, C9.2, C10.2, C11.2, C12.2, C13.2, C14.2, C15.2, C16.2, C17.2, C18.2, C19.2, C20.2, C21.2, C22.2, C23.2, C24.2, C25.2, C26.2, C35.2, C36.2, C38.2, C39.1, C40.2, C41.1, C42.2, C43.2, C44.2, J1.A1, J1.A2, J1.B1, J1.B2, J1.B43, J1.B44, J1.B45, J1.B46, J2.2, J2.10, J3.1, J3.10, J3.17, J3.26, J4.1, J4.10, J4.17, J4.26, R2.2, R4.2, R27.1, R29.1, R30.1, R33.1, SW1.1, SW1.3, TP2.1, U1.4, U2.19, U2.21, U2.27, U2.36, U2.41, U2.48, U2.57, U2.63, U2.82, U2.94, U2.95, U2.96, U2.97, U2.108, U2.118, U2.123, U2.131, U2.140, U2.PAD, U11.0, U11.8, U12.2, X1.2
Net-<C37-Pad1>: C37.1, R30.2, R31.1, U11.1
Net-<C42-Pad1>: C42.1, U12.4
Net-<L1-Pad2>: L1.2, U11.10
Net-<L2-Pad1>: L2.1, U11.6
Net-<R10-Pad2>: R10.2, U1.3
Net-<R11-Pad2>: R11.2, SW1.4, U1.2
Net-<R12-Pad2>: R12.2, SW1.2, U1.1
Net-<R13-Pad2>: R13.2, TP1.1, U1.7
Net-<R27-Pad2>: R27.2, R28.2, U11.2
Net-<R29-Pad2>: R29.2, R32.1, U11.5
